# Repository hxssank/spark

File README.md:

# Spark

A compact power-bank development project that connects enclosure CAD, circuit design, component placement and an interactive review UI. The work currently includes a routed bench boost-converter PCB and several compact packaging studies.

The CAD checks component reservations. The power model solves current, voltage sag and energy loss. [The engineering walkthrough](ENGINEERING.md) derives the equations and identifies the missing measurements.

*Existing CAD render of Prototype A. It shows the intended enclosure; it is not a tested consumer power bank.*

## Open the hardware files

| File | Contents |
| --- | --- |
| [Assembly STEP](mechanical/exports/spark_assembly.step) | Prototype A enclosure and component reservations |
| [Print STLs](mechanical/print_parts/) | Sleeve, carrier, front cover and bottom cap for fit prototypes |
| [Compact STEP models](mechanical/compact-exports/) | Separate 300, 530 and 850 mAh packing studies |
| [KiCad schematic](electronics/boost-prototype/spark_boost_rev_a.kicad_sch) and [PDF](electronics/boost-prototype/reports/schematic.pdf) | TPS61288 bench boost circuit |
| [KiCad board](electronics/boost-prototype/spark_boost_rev_a.kicad_pcb) and [board preview](electronics/boost-prototype/preview/pcb-front.svg) | Routed four-layer bench board |
| [Board BOM](electronics/boost-prototype/BOM.csv) | References, values, candidate manufacturer parts and unresolved selections |
| [Compact 850 parts](sourcing/digikey-canada-compact-850.csv) | Dated sourcing candidates and purchase conditions |
| [Gerbers and drills](electronics/boost-prototype/manufacturing-review/) | Engineering-review exports with [stackup and limits](electronics/boost-prototype/manufacturing-review/status.json) |
| [DRC report](electronics/boost-prototype/reports/pcb-drc.json) | KiCad 10.0.7 check of the included board and schematic |

The November 9 exports passed DRC with zero violations, unconnected items or schematic-parity issues; no checks were disabled. The four print meshes are connected and watertight. These are geometry and circuit-file checks, not physical fit or electrical measurements. The Gerbers describe the bench converter, not a complete battery charger or USB-C power bank.

## What is implemented

- Parametric CadQuery enclosure and internal component models.
- A four-layer 5 V/9 V boost-converter bench PCB with KiCad schematic, board, symbols and footprints.
- Compact 300, 530 and 850 mAh placement studies with dimensions checked against their component reservations.
- Three.js review code for assembly views, scale comparisons, display behavior and component inspection.
- Analytical energy and resistance models that label their assumptions and reject invalid inputs.
- Automated checks for circuit consistency, geometry, asset publication and package integrity.

## Separate the bench board from the product target

| Design | Current state |
| --- | --- |
| Prototype A | 116 x 24 x 14.8 mm enclosure study and routed bench boost PCB |
| Compact 850 | 99 x 24 x 12 mm packaging target and a 25 W electrical target |
| Compact 300/530 | Smaller cell and component-reservation studies |
| Complete phone power bank | USB-PD, charging, independent protection, temperature cutoff and final interconnects still require implementation and validation |

No measured 25 W output, charging performance or battery runtime is claimed. The converter layout and enclosure calculations do not qualify cell behavior, temperature rise or loop stability.

## Engineering work to inspect

| Path | What it contains |
| --- | --- |
| [`electronics/boost-prototype/`](electronics/boost-prototype/) | Bench schematic/PCB, placement data, generators and circuit checks |
| [`electronics/compact-design/layout.json`](electronics/compact-design/layout.json) | Compact part reservations and board-face placement |
| [`mechanical/build_model.py`](mechanical/build_model.py) | Prototype A CAD, fit checks and export generation |
| [`mechanical/build_compact_model.py`](mechanical/build_compact_model.py) | Compact placement CAD and dimension validation |
| [`review/`](review/) | Assembly viewer, interaction controls and analytical comparison UI |
| [`scripts/`](scripts/) | Verification and package-integrity tooling |
| [`sourcing/`](sourcing/) | Dated candidate parts and purchase gates |

The assembly checks distinguish physical parts from reservations. The display starts with unknown readings; simulated telemetry requires an explicit demo mode. The energy model accounts for conversion loss and resistance, and hides results when a scenario violates its limits.

## Rebuild the CAD

Use a Python environment compatible with CadQuery 2.8.0.

```sh
python -m venv .venv
.venv/bin/python -m pip install -r mechanical/requirements.txt
.venv/bin/python mechanical/build_model.py
.venv/bin/python mechanical/build_compact_model.py
```

On Windows, use `.venv\Scripts\python.exe` for the Python commands. The generators produce STEP, STL and GLB outputs from the included source. Ready-to-open STEP models, print STLs and bench-board exports are included; cached build environments are excluded.

## Check the source

```sh
.venv/bin/python -m pytest -q mechanical/test_compact_model.py mechanical/test_publish_assets.py electronics/boost-prototype/test_circuit_checks.py
cd review
npm ci
npm run test:source
```

The November 9, 2026 publication checks passed **35 selected Python tests and all 83 review Node tests**. Both CAD generators and the review-page build also completed. The 48-test Node source subset covers compact placement, display states, energy calculations, fit summaries, motion scheduling and viewer controls. It does not require a hardware board. Full asset and packaging tests additionally require regenerated CAD, preview and render outputs.

After CAD generation, run `npm run build` in `review/` to build the review pages. Serve the repository root with `python -m http.server 8000 --bind 127.0.0.1` and open `http://127.0.0.1:8000/review/`.

The October 30 project record reports 187 Python tests, 83 Node tests and zero ERC/DRC findings for that complete local snapshot. Those historical results do not establish that every generated artifact in a fresh checkout is current. The public snapshot's validation scope is stated above.

## Next hardware work

Complete the USB-C, charging, protection and sensing circuits. Resolve actual connector and cell dimensions, then test the converter with a laboratory supply and electronic load before connecting a battery. Measure loop stability, current-path losses, temperature and fault cutoff before claiming phone-charging capability.

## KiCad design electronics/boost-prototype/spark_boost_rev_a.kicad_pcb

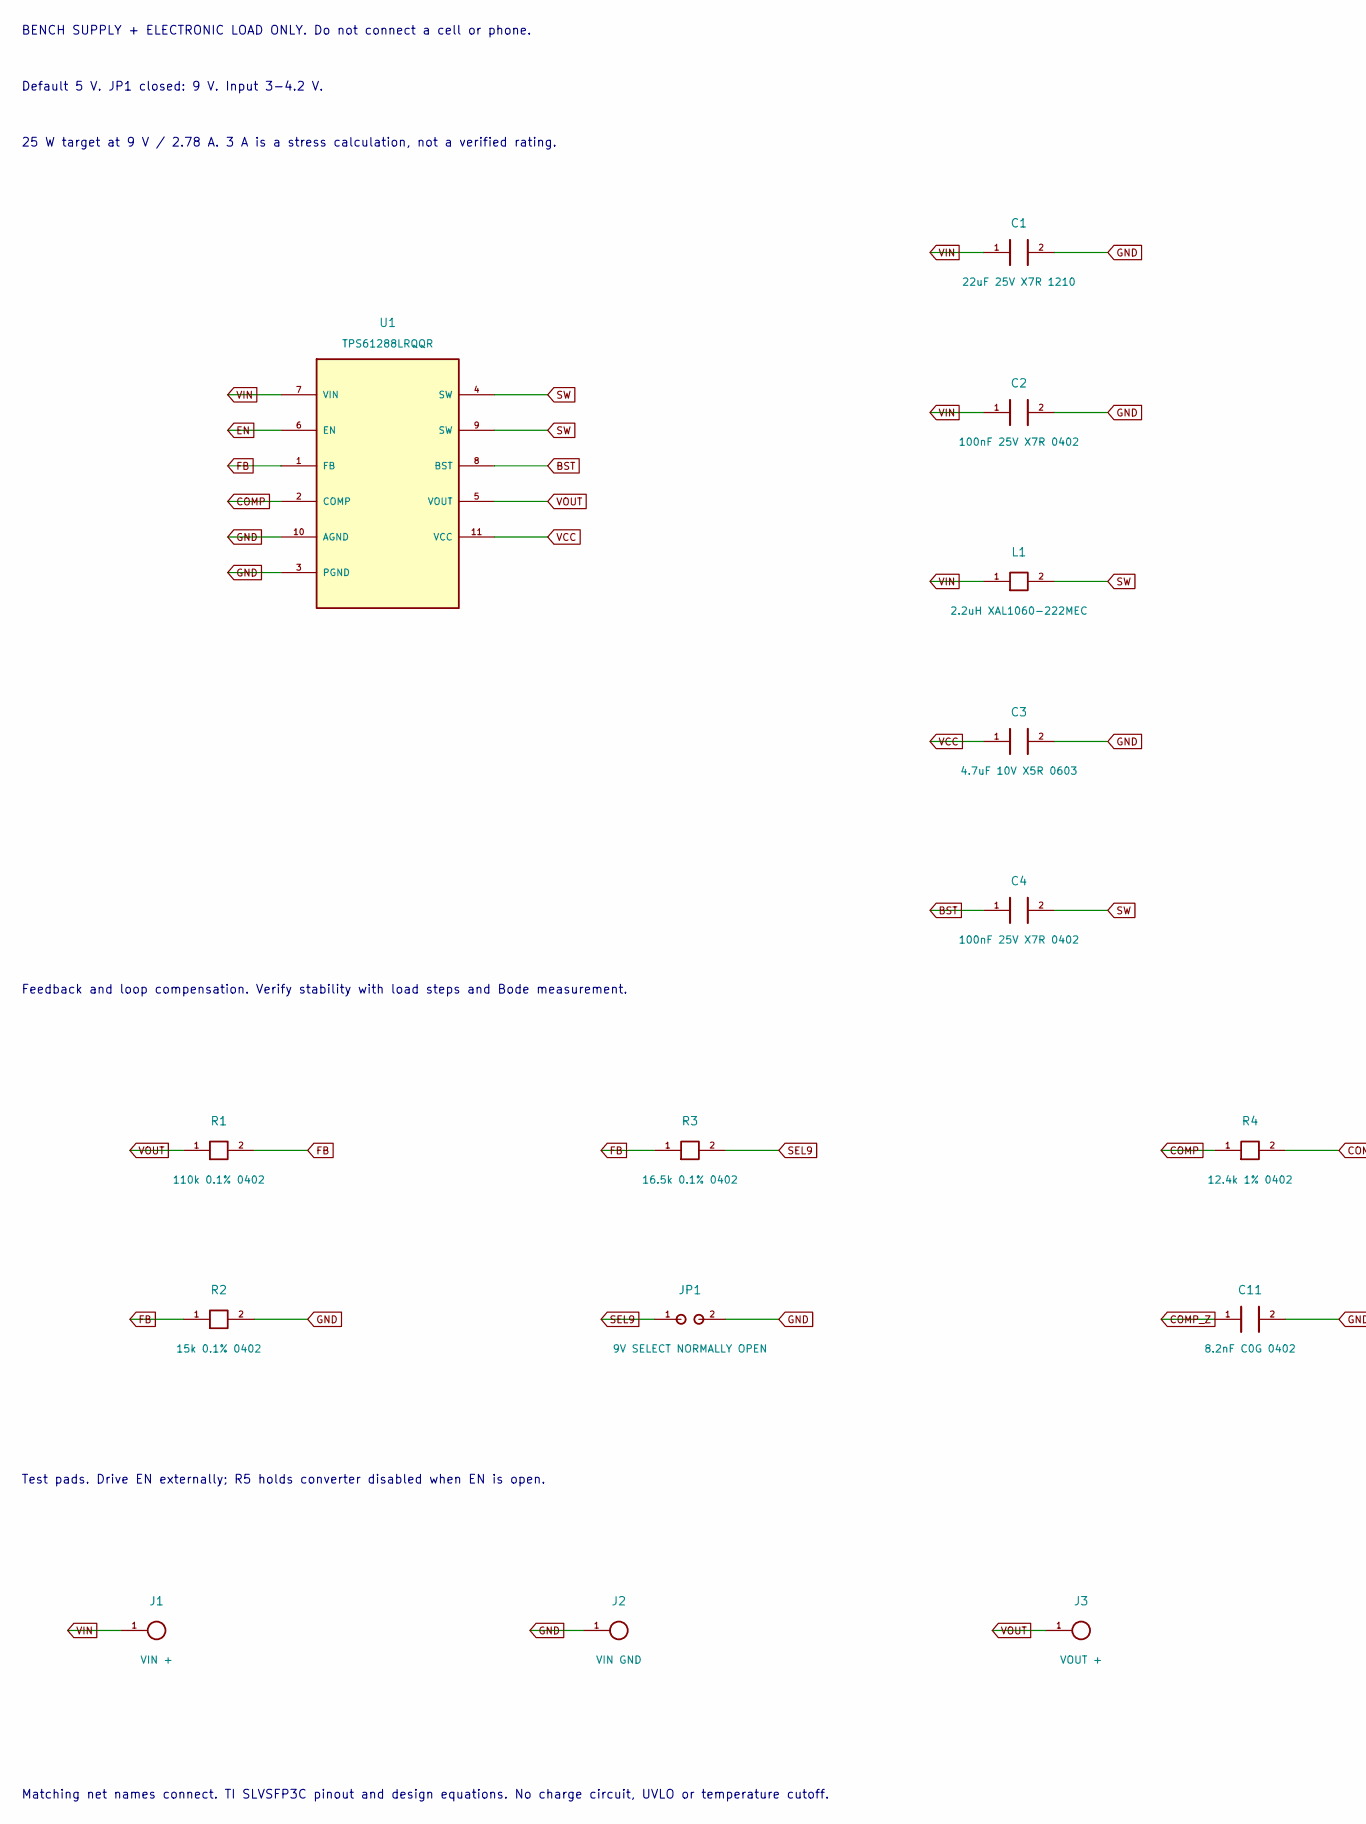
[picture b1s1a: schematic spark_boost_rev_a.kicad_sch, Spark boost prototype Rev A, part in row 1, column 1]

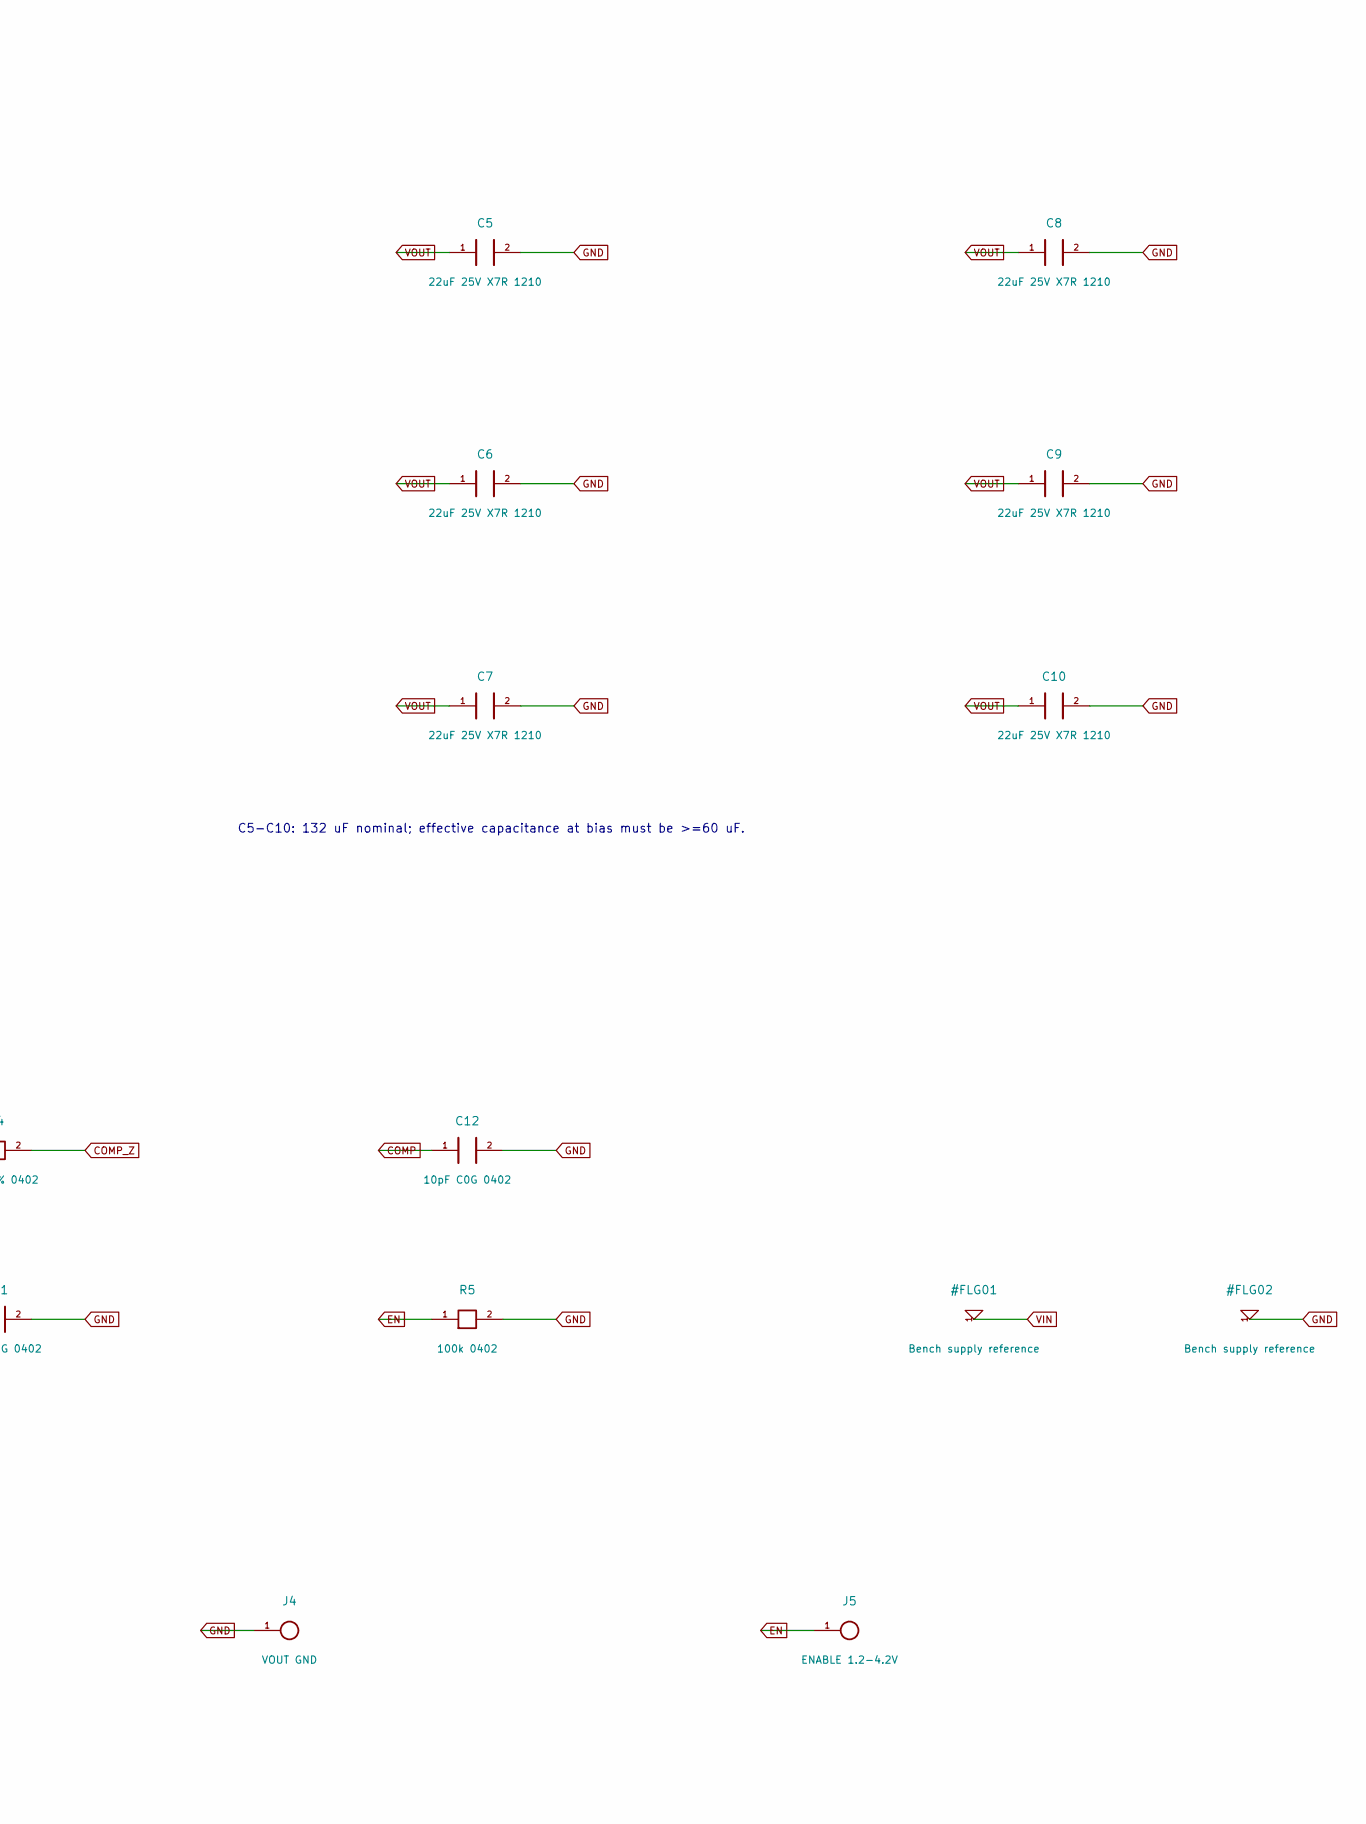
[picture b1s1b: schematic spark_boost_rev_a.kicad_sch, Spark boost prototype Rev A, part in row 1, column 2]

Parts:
C1: 22uF 25V X7R 1210; C1_C_1210
C2: 100nF 25V X7R 0402; C2_C_0402
C3: 4.7uF 10V X5R 0603; C3_C_0603
C4: 100nF 25V X7R 0402; C4_C_0402
C5: 22uF 25V X7R 1210; C5_C_1210
C6: 22uF 25V X7R 1210; C6_C_1210
C7: 22uF 25V X7R 1210; C7_C_1210
C8: 22uF 25V X7R 1210; C8_C_1210
C9: 22uF 25V X7R 1210; C9_C_1210
C10: 22uF 25V X7R 1210; C10_C_1210
C11: 8.2nF C0G 0402; C11_C_0402
C12: 10pF C0G 0402; C12_C_0402
J1: VIN +; J1_WirePad
J2: VIN GND; J2_WirePad
J3: VOUT +; J3_WirePad
J4: VOUT GND; J4_WirePad
J5: ENABLE 1.2-4.2V; J5_WirePad
JP1: 9V SELECT NORMALLY OPEN; JP1_J_SolderJumper_OPEN
L1: 2.2uH XAL1060-222MEC; L1_Coilcraft_XAL1060
R1: 110k 0.1% 0402; R1_R_0402
R2: 15k 0.1% 0402; R2_R_0402
R3: 16.5k 0.1% 0402; R3_R_0402
R4: 12.4k 1% 0402; R4_R_0402
R5: 100k 0402; R5_R_0402
U1: TPS61288LRQQR; U1_TPS61288_RQQ0011A

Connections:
BST: C4.1, U1.8 (BST)
COMP: C12.1, R4.1, U1.2 (COMP)
COMP_Z: C11.1, R4.2
EN: J5.1, R5.1, U1.6 (EN)
FB: R1.2, R2.1, R3.1, U1.1 (FB)
GND: C1.2, C2.2, C3.2, C5.2, C6.2, C7.2, C8.2, C9.2, C10.2, C11.2, C12.2, J2.1, J4.1, JP1.2, R2.2, R5.2, U1.3 (PGND), U1.10 (AGND)
SEL9: JP1.1, R3.2
SW: C4.2, L1.2, U1.4 (SW), U1.9 (SW)
VCC: C3.1, U1.11 (VCC)
VIN: C1.1, C2.1, J1.1, L1.1, U1.7 (VIN)
VOUT: C5.1, C6.1, C7.1, C8.1, C9.1, C10.1, J3.1, R1.1, U1.5 (VOUT)

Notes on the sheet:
BENCH SUPPLY + ELECTRONIC LOAD ONLY. Do not connect a cell or phone.
Default 5 V. JP1 closed: 9 V. Input 3-4.2 V.
25 W target at 9 V / 2.78 A. 3 A is a stress calculation, not a verified rating.
C5-C10: 132 uF nominal; effective capacitance at bias must be >=60 uF.
Feedback and loop compensation. Verify stability with load steps and Bode measurement.
Test pads. Drive EN externally; R5 holds converter disabled when EN is open.
Matching net names connect. TI SLVSFP3C pinout and design equations. No charge circuit, UVLO or temperature cutoff.

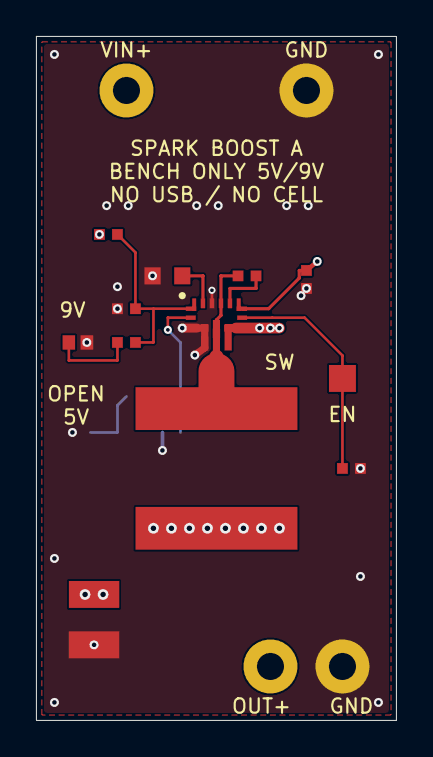
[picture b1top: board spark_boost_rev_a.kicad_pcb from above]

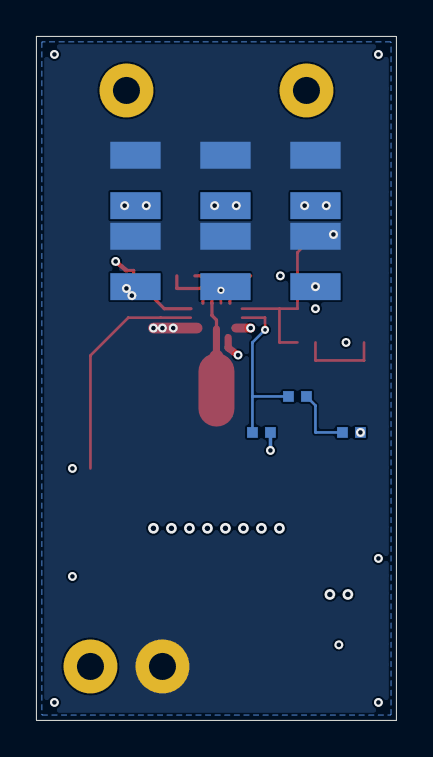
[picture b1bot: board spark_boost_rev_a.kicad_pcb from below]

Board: 4 copper layers, 20.0 x 38.0 mm, 25 parts (9 on the bottom side), 11 nets.

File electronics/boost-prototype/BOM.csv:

Reference,Quantity,Value,Manufacturer,MPN,Footprint,Status,Source
U1,1,TPS61288LRQQR,Texas Instruments,TPS61288LRQQR,Spark:U1_TPS61288_RQQ0011A,Manufacturer part and pin map verified,https://www.ti.com/lit/ds/symlink/tps61288.pdf
L1,1,2.2uH XAL1060-222MEC,Coilcraft,XAL1060-222MEC,Spark:L1_Coilcraft_XAL1060,"Manufacturer value, dimensions and land pattern verified",https://www.coilcraft.com/getmedia/8909f858-b441-4d60-acff-8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
C1,1,22uF 25V X7R 1210,Murata,GRM32ER71E226KE15L,Spark:C1_C_1210,Datasheet dimensions verified; effective capacitance and sourcing unverified,https://search.murata.co.jp/Ceramy/image/img/A01X/G101/ENG/G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
C2,1,100nF 25V X7R 0402,,,Spark:C2_C_0402,Specification only; exact manufacturer part and ratings still require selection,
C3,1,4.7uF 10V X5R 0603,KYOCERA AVX,0603ZD475KAT2A,Spark:C3_C_0603,TI EVM VCC capacitor part; effective capacitance must be confirmed,https://www.ti.com/lit/pdf/SLVUBW6
C4,1,100nF 25V X7R 0402,,,Spark:C4_C_0402,Specification only; exact manufacturer part and ratings still require selection,
C5,1,22uF 25V X7R 1210,Murata,GRM32ER71E226KE15L,Spark:C5_C_1210,Datasheet dimensions verified; effective capacitance and sourcing unverified,https://search.murata.co.jp/Ceramy/image/img/A01X/G101/ENG/G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
C6,1,22uF 25V X7R 1210,Murata,GRM32ER71E226KE15L,Spark:C6_C_1210,Datasheet dimensions verified; effective capacitance and sourcing unverified,https://search.murata.co.jp/Ceramy/image/img/A01X/G101/ENG/G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
C7,1,22uF 25V X7R 1210,Murata,GRM32ER71E226KE15L,Spark:C7_C_1210,Datasheet dimensions verified; effective capacitance and sourcing unverified,https://search.murata.co.jp/Ceramy/image/img/A01X/G101/ENG/G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
C8,1,22uF 25V X7R 1210,Murata,GRM32ER71E226KE15L,Spark:C8_C_1210,Datasheet dimensions verified; effective capacitance and sourcing unverified,https://search.murata.co.jp/Ceramy/image/img/A01X/G101/ENG/G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
C9,1,22uF 25V X7R 1210,Murata,GRM32ER71E226KE15L,Spark:C9_C_1210,Datasheet dimensions verified; effective capacitance and sourcing unverified,https://search.murata.co.jp/Ceramy/image/img/A01X/G101/ENG/G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
C10,1,22uF 25V X7R 1210,Murata,GRM32ER71E226KE15L,Spark:C10_C_1210,Datasheet dimensions verified; effective capacitance and sourcing unverified,https://search.murata.co.jp/Ceramy/image/img/A01X/G101/ENG/G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
R1,1,110k 0.1% 0402,,,Spark:R1_R_0402,Specification only; exact manufacturer part and ratings still require selection,
R2,1,15k 0.1% 0402,,,Spark:R2_R_0402,Specification only; exact manufacturer part and ratings still require selection,
R3,1,16.5k 0.1% 0402,,,Spark:R3_R_0402,Specification only; exact manufacturer part and ratings still require selection,
JP1,0,9V SELECT NORMALLY OPEN,,,Spark:JP1_J_SolderJumper_OPEN,PCB feature; no purchased component,
R4,1,12.4k 1% 0402,,,Spark:R4_R_0402,Specification only; exact manufacturer part and ratings still require selection,
C11,1,8.2nF C0G 0402,,,Spark:C11_C_0402,Specification only; exact manufacturer part and ratings still require selection,
C12,1,10pF C0G 0402,,,Spark:C12_C_0402,Specification only; exact manufacturer part and ratings still require selection,
R5,1,100k 0402,,,Spark:R5_R_0402,Specification only; exact manufacturer part and ratings still require selection,
J1,0,VIN +,,,Spark:J1_WirePad,PCB feature; no purchased component,
J2,0,VIN GND,,,Spark:J2_WirePad,PCB feature; no purchased component,
J3,0,VOUT +,,,Spark:J3_WirePad,PCB feature; no purchased component,
J4,0,VOUT GND,,,Spark:J4_WirePad,PCB feature; no purchased component,
J5,0,ENABLE 1.2-4.2V,,,Spark:J5_WirePad,PCB feature; no purchased component,
